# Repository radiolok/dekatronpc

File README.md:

# DekatronPC

Ламповый компьютер на декатронах А110 с системой команд Brainfuck. Счётчики машины — реверсивные декатроны: они умеют ровно то, что нужно Brainfuck, — прибавить и отнять единицу. Логика вокруг них — вакуумные лампы 6Н16Б и 6Ж2Б, без кремниевых полупроводников в вычислительном тракте.

*A vacuum-tube Brainfuck computer built around A110 dekatron counting tubes. RTL in SystemVerilog, an FPGA emulator for blocks not yet built, requirements and microarchitecture docs in Russian.*

## Машина

| Параметр | Значение |
|---|---|
| Архитектура | гарвардская: отдельные память программ и память данных |
| Система команд | один набор из 16 опкодов (ISA16): Brainfuck и шесть служебных, 4 бита на команду |
| Счётчик команд IP | 5 декатронов, 0…99999 |
| Счётчик вложенности Loop | 2 декатрона, 0…99; переполнение — аппаратная ошибка, машина замирает до сброса |
| Указатель данных AP | 5 декатронов; в RTL счёт замыкается 0 ↔ 99999 (предел 29999 — открытый вопрос OPEN-001) |
| Значение ячейки Data | 3 декатрона, 0…255 |
| Всего декатронов | 15 |
| Память программ | 100 000 × 4 бит, верхняя декада 99990…99999 — ПЗУ загрузчика |
| Память данных | 100 000 ячеек × 10 бит (BCD: сотни, десятки, единицы); физически — ферритовые кубы КП128/17-М70, до их установки память играет эмулятор на ПЛИС |
| Тактовая частота | 100 кГц (сборка по умолчанию; статический анализ по SPICE-задержкам ламп даёт минимальный период ≈ 9 мкс; тайминги самого декатрона — OPEN-013/014) |
| Логика | ≈ 1070 ламп + 15 декатронов А110 по синтезу RTL в библиотеку спроектированных ламповых ячеек (среднее по четырём зёрнам ABC, ±10), без памяти; бюджет 1200, цель — меньше 1000 |

Адреса и данные хранятся в BCD прямо так, как их показывают декатроны: память адресуется тетрадами без перевода в двоичный код. Цикл просматривается самой линией выборки: при `[` с нулевой ячейкой или `]` с ненулевой IP проматывается до парной скобки, счётчик Loop считает вложенность.

Конфигурация счётчиков проверена на наборе из ста реальных программ с GitHub — [Brainfuck-100](https://github.com/radiolok/bfutils/tree/master/programs/bf100) в сабмодуле `bfutils`: в 5 + 2 + 5 + 3 декатрона помещаются 97 программ из 100.

## Система команд

Один 4-битный набор, режимов нет (ISA16, [doc/isa16.md](doc/isa16.md)). Коды 0x0…0xA — Brainfuck.

| Опкод | Символ | Команда |
|---|---|---|
| 0x0 | `N` | NOP |
| 0x1 | `H` | HALT |
| 0x2 / 0x3 | `+` `-` | INC / DEC ячейки |
| 0x4 / 0x5 | `>` `<` | AINC / ADEC |
| 0x6 / 0x7 | `[` `]` | цикл по нулю ячейки |
| 0x8 / 0x9 | `.` `,` | COUT / CIN |
| 0xA | `0` | `[-]` — ячейка ← 0 (ставит MemLock) |
| 0xB | `S` / `E` | LD — начало загрузки; в потоке загрузки — её конец (EOT), в память не пишется |
| 0xC | `A` | CLRA — AP ← 0 |
| 0xD | `P` | MemLock — ставит флаг MemLock без загрузки: ячейка ← счётчик данных (копирование `>P<`) |
| 0xE / 0xF | `{` `}` | цикл по нулю AP (нужен загрузчику) |

Промотка считает `[ ]` и `{ }` вместе, поэтому вкладывать один вид в другой нельзя. Аппаратный сброс ставит IP = 99990 и запускает загрузчик `0<{0<}` … LD из верхней декады памяти программ, защищённой от записи (очистка памяти данных и загрузка с адреса 0); программный сброс обнуляет все счётчики, в том числе IP. EOT запускает программный сброс. Полная семантика, MemLock и ленивое чтение памяти данных — в [TRS.md](TRS.md), разделы 6–10.

## Документы

| Документ | Что в нём |
|---|---|
| [TRS.md](TRS.md) | требования: архитектура, ISA, память, декатроны, RTL, верификация, стенд, ламповые модули, открытые вопросы, чек-лист и план работ. Каждое требование имеет ID (`REQ-*`, `OPEN-*`) и статус |
| [SCHEMES.md](SCHEMES.md) | структурные схемы ядра в семи листах: декатрон, модуль, счётчик, IpLine, ApLine, MachineCtrl, верхний уровень |
| [doc/dpcrun_golden_model.md](doc/dpcrun_golden_model.md) | C++ golden model: семантика, расхождения RTL и TRS, найденные дефекты |
| [tb/README.md](tb/README.md) | testbench на cocotb и pyuvm |
| [doc/isa16.md](doc/isa16.md) | система команд ISA16 и выбор между вариантами |
| [doc/tube_count_below_1000.md](doc/tube_count_below_1000.md) | путь подсчёта ламп: что сделано и что отвергнуто (ранее — `doc/tube_count_reduction.md`, `doc/tube_count_1000.md`) |
| [sch/logic/README.md](sch/logic/README.md) | библиотека ламповых ячеек: SPICE, схемы KiCad, страницы ячеек; метод — [doc/cell_design_method.md](doc/cell_design_method.md) |
| [doc/vtube_sta.md](doc/vtube_sta.md), [doc/synth_sim.md](doc/synth_sim.md) | статический анализ времён и симуляция нетлиста с задержками ламп |
| [rtl/DekatronPC/Dekatron/DekatronCounter.md](rtl/DekatronPC/Dekatron/DekatronCounter.md) | устройство декатронного счётчика |
| [rtl/DekatronPC/emulator_inspection.md](rtl/DekatronPC/emulator_inspection.md) | разбор слоя эмулятора на ПЛИС |
| [history.md](history.md) | журнал сессий работы над проектом |

## Репозиторий

| Путь | Содержимое |
|---|---|
| `rtl/DekatronPC/` | ядро: `DekatronPC.sv`, `MachineCtrl.sv`, `IpLine.sv`, `ApLine.sv`, `IpMemory.sv`, `RAM.sv`, верх для DE0-Nano `De0Nano.sv` |
| `rtl/DekatronPC/Dekatron/` | декатрон: модель лампы `DekatronTubeV2`, модуль, счётчик, генератор фаз, формирователь импульсов |
| `rtl/parameters.sv` | разрядность счётчиков |
| `rtl/Emulator/` | слой эмулятора на ПЛИС: клавиатура, индикатор МС6205, ИН-12, загрузчик прошивки |
| `rtl/Logic/`, `rtl/Functions/` | примитивы и кодеры |
| `sch/logic/` | ламповые логические ячейки, по папке на ячейку (схема, тестбенч, описание, картинки; перечень в `sch/logic/README.md`), и библиотека ячеек для синтеза `vtube_cells.lib` / `vtube_cells.v` / `vtube_timing.json` |
| `rtl/programs/` | тестовые программы `*.bfk` и загрузчик |
| `rtl/run/` | скрипты моделирования, синтеза и подсчёта ламп |
| `rtl/quartus/` | проект Quartus |
| `tb/` | testbench на cocotb и pyuvm |
| `bfutils/` | сабмодуль [radiolok/bfutils](https://github.com/radiolok/bfutils): компилятор, эмулятор, golden model `dpcrun`, набор Brainfuck-100 |
| `sch/` | схемы KiCad: эмулятор, экспериментальная декатронная ячейка, библиотеки ламп, ферритовая память (`sch/fcore`), блок питания стенда (`sch/stand`) |
| `doc/` | отчёты и справочная литература |
| `img/schemes/` | картинки для SCHEMES.md |
| `web/` | симулятор в браузере: пульт, декатроны, загрузка по SOT/EOT, Brainfuck-100 ([web/README.md](web/README.md)) |
| `tools/` | `spice/` (расчёт ячеек), `kicad/` (генераторы схем), `digitize/` (оцифровка справочников), `netview/` (схемы нетлиста), `synth/`, `bf100/` |
| `tools/schemes/` | генератор SCHEMES.md и картинок схем: `python3 tools/schemes/build.py` |

Блоки `Dekatron.sv`, `DekatronPulseAllow`, `DekatronCarrySignal`, `InsnDecoder`, `BcdToBinEnc` в тракте памяти и папка `rtl/[DEPRECATED]` — старый тракт, подлежит удалению (TRS, раздел 19.4).

## Сборка и проверка

```bash
git clone --recursive https://github.com/radiolok/dekatronpc.git
cd dekatronpc
git submodule update --init       # если клонировали без --recursive

docker build -t dekatron-pc .     # Verilator, Icarus, Yosys, cocotb — то же окружение, что в CI
# Quartus собирается отдельно: ./rtl/run/build_fpga.sh, CI — .github/workflows/fpga.yml
```

| Задача | Команда |
|---|---|
| один тест на Icarus | `cd tb && make test_compare SIM=icarus` |
| регрессия cocotb | `cd tb && make regression` |
| моделирование RTL | `cd rtl/run && ./run_tests.sh -t` |
| то же с моделью задержек ламп | `cd rtl/run && ./run_tests.sh -d` |
| синтез в лампы (Yosys), подсчёт ламп | `cd rtl/run && ./run_tests.sh -s` |
| RTL-тесты на нетлисте (`-t` — с задержками ламп) | `cd rtl/run && ./synth_sim.sh [-t]` |

Полная сборка DekatronPC и эмулятора в Verilator и синтез — тяжёлые задачи; на слабой машине начинайте с одиночных целей на Icarus. CI: `.github/workflows/` (`docker-image.yml`, `fpga.yml`, `web.yml`, `pages.yml`).

## Состояние

Версия требований — TRS v0.53 (2026-11-04).

- Готово в RTL: ISA16, модель декатрона и счётчик с завершением операции в такте приёма, IpLine / ApLine / MachineCtrl с предвыборкой и MemLock, банковая память, загрузчик в верхней декаде, терминал по UART.
- Проверка: golden model `bfutils/dpcrun` совпадает с RTL шаг в шаг (pi.bfk — 221 386 шагов, вывод `3.141`); cocotb, Icarus, Verilator, синтез и симуляция нетлиста (в том числе с задержками ламп из SPICE) идут в CI; есть симулятор в браузере.
- Ламповые ячейки (NOR, NAND, AOI, защёлки, триггеры) рассчитаны в SPICE и нарисованы в KiCad; на железе подтверждены только отдельные измерения (ёмкость ламп, блок питания).
- Открыто: OPEN-001 (предел AP), OPEN-007 (BELL), OPEN-011, OPEN-012, OPEN-013/014 (тайминги декатрона), OPEN-018. Следующие этапы: P&R-инструмент (REQ-PR-*), платы модуля декатрона, испытательный стенд, ферритовая память, первые ламповые модули.

Полный чек-лист — в TRS.md, разделы 19–22.

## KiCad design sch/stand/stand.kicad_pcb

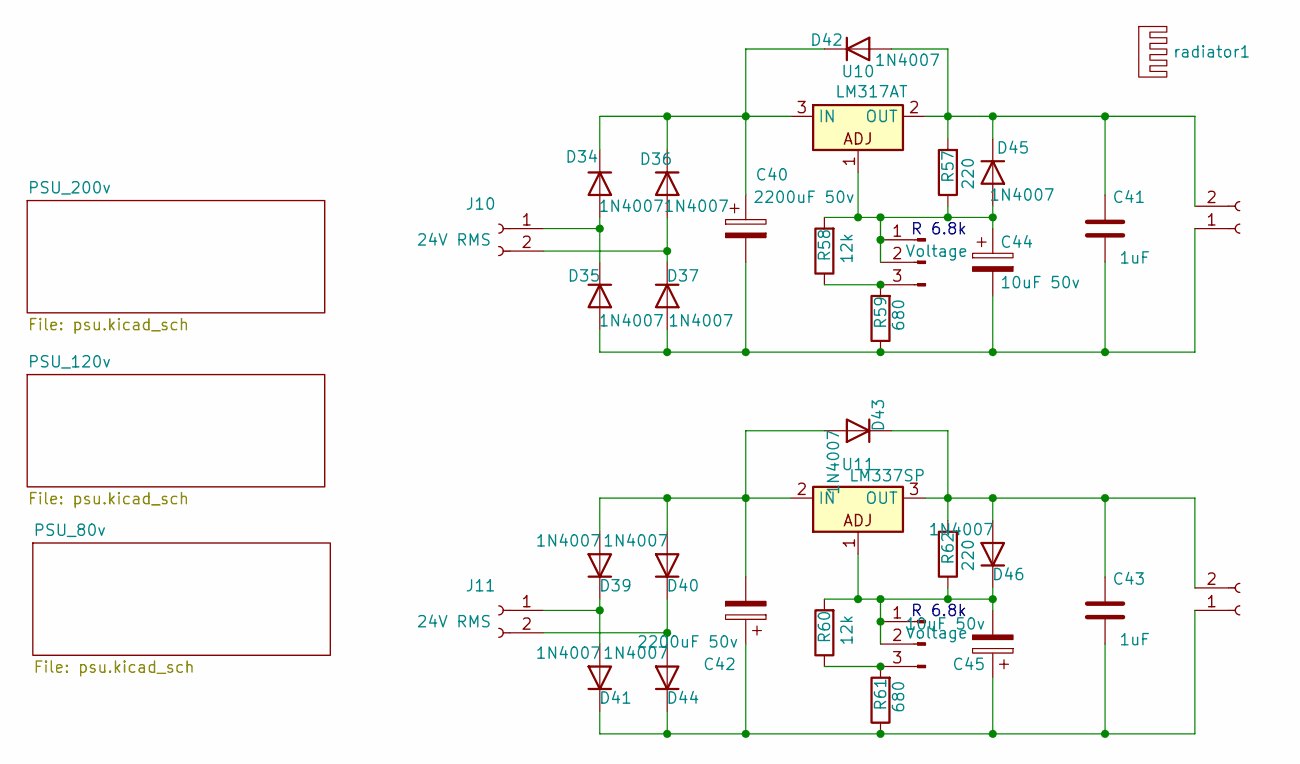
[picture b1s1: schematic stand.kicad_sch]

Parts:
C40, C42: 2200uF 50v; CP_Radial_D18.0mm_P7.50mm
C41, C43: 1uF; C_Axial_L3.8mm_D2.6mm_P7.50mm_Horizontal
C44, C45: 10uF 50v; CP_Radial_D10.0mm_P3.50mm
D34, D35, D36, D37, D39, D40, D41, D42, D43, D44, D45, D46: 1N4007; D_DO-41_SOD81_P10.16mm_Horizontal
J10, J11: 24V RMS; TerminalBlock_Phoenix_MKDS-1,5-2-5.08_1x02_P5.08mm_Horizont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
J12, J13: Vout; TerminalBlock_Phoenix_MKDS-1,5-2-5.08_1x02_P5.08mm_Horizont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
J14, J15: Voltage; PinHeader_1x03_P2.54mm_Vertical
R57, R62: 220; R_Axial_DIN0207_L6.3mm_D2.5mm_P7.62mm_Horizontal
R58, R60: 12k; R_Axial_DIN0207_L6.3mm_D2.5mm_P7.62mm_Horizontal
R59, R61: 680; R_Axial_DIN0207_L6.3mm_D2.5mm_P7.62mm_Horizontal
U10: LM317AT; TO-220-3_Vertical
U11: LM337SP; TO-220-3_Vertical
radiator1: Радиатор

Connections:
unnamed: D34.2 (A), D35.1 (K), J10.1
unnamed: C40.1, D34.1 (K), D36.1 (K), D42.1 (K), U10.3 (IN)
unnamed: C40.2, C41.2, C44.2, D35.2 (A), D37.2 (A), J12.1, R59.1
unnamed: D36.2 (A), D37.1 (K), J10.2
unnamed: C42.2, D39.2 (A), D40.2 (A), D43.2 (A), U11.2 (IN)
unnamed: D39.1 (K), D41.2 (A), J11.1
unnamed: D40.1 (K), D44.2 (A), J11.2
unnamed: C42.1, C43.2, C45.1, D41.1 (K), D44.1 (K), J13.1, R61.1
unnamed: C41.1, D42.2 (A), D45.1 (K), J12.2, R57.2, U10.2 (OUT)
unnamed: C43.1, D43.1 (K), D46.2 (A), J13.2, R62.2, U11.3 (OUT)
unnamed: C44.1, D45.2 (A), J14.1, J14.2, R57.1, R58.2, U10.1
unnamed: C45.2, D46.1 (K), J15.1, J15.2, R60.2, R62.1, U11.1
unnamed: J14.3, R58.1, R59.2
unnamed: J15.3, R60.1, R61.2

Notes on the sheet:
R 6.8k

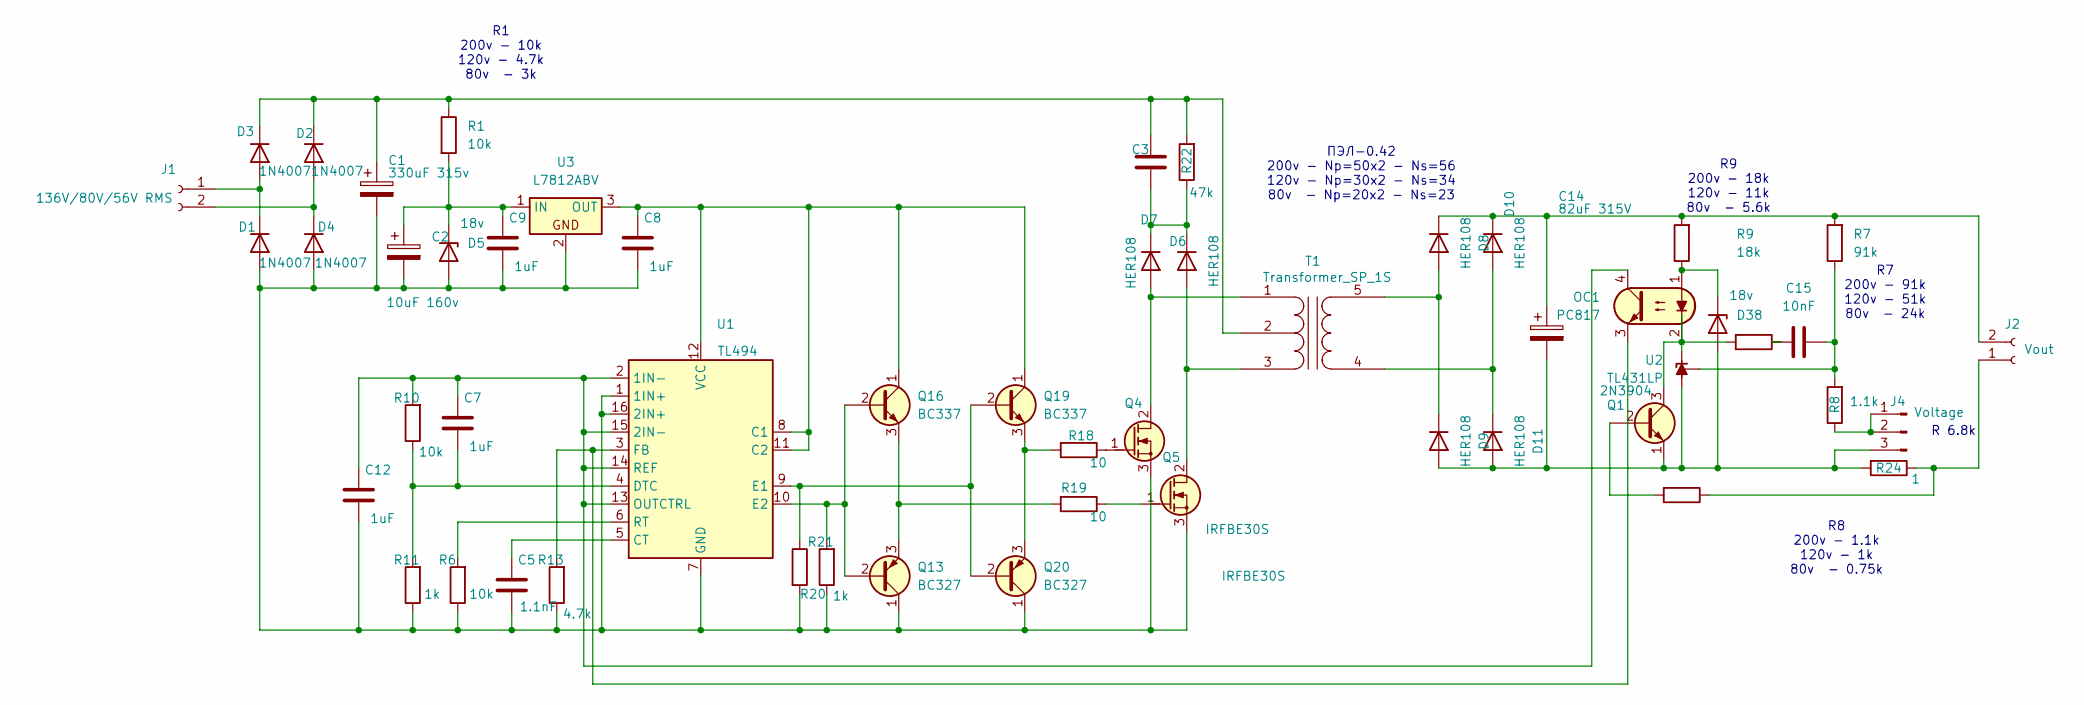
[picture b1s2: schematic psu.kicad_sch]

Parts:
C1: 330uF 315v; CP_Radial_D30.0mm_P10.00mm_SnapIn
C2: 10uF 160v; CP_Radial_D10.0mm_P3.50mm
C3: 10nF 630v; C_Rect_L11.5mm_W6.4mm_P10.00mm_MKT
C5: 1.1nF; C_Axial_L3.8mm_D2.6mm_P7.50mm_Horizontal
C7, C8, C9, C12: 1uF; C_Axial_L3.8mm_D2.6mm_P7.50mm_Horizontal
C14: 82uF 315V; CP_Radial_D18.0mm_P7.50mm
C15: 10nF; C_Rect_L7.0mm_W2.5mm_P5.00mm
D1, D2, D3, D4: 1N4007; D_DO-41_SOD81_P10.16mm_Horizontal
D5, D38: 18v; D_DO-35_SOD27_P7.62mm_Horizontal
D6, D7, D8, D9, D10, D11: HER108; D_DO-41_SOD81_P10.16mm_Horizontal
J1: 136V/80V/56V RMS; TerminalBlock_Phoenix_MKDS-1,5-2-5.08_1x02_P5.08mm_Horizont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
J2: Vout; TerminalBlock_Phoenix_MKDS-1,5-2-5.08_1x02_P5.08mm_Horizont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
J4: Voltage; PinHeader_1x03_P2.54mm_Vertical
OC1: PC817; DIP-4_W7.62mm_LongPads
Q1: 2N3904; TO-92_Inline_Wide_EBC
Q4, Q5: IRFBE30S; TO-263-2
Q13, Q20: BC327; TO-92_Inline_Wide_CBE
Q16, Q19: BC337; TO-92_Inline_Wide_CBE
R1: 10k; R_Axial_DIN0918_L18.0mm_D9.0mm_P25.40mm_Horizontal
R6, R10: 10k; R_Axial_DIN0207_L6.3mm_D2.5mm_P7.62mm_Horizontal
R7: 91k; R_Axial_DIN0516_L15.5mm_D5.0mm_P5.08mm_Vertical
R8: 1.1k; R_Axial_DIN0207_L6.3mm_D2.5mm_P7.62mm_Horizontal
R9: 18k; R_Axial_DIN0516_L15.5mm_D5.0mm_P5.08mm_Vertical
R11: 1k; R_Axial_DIN0207_L6.3mm_D2.5mm_P7.62mm_Horizontal
R13: 4.7k; R_Axial_DIN0207_L6.3mm_D2.5mm_P7.62mm_Horizontal
R18, R19: 10; R_Axial_DIN0207_L6.3mm_D2.5mm_P7.62mm_Horizontal
R20, R21: 1k; R_Axial_DIN0617_L17.0mm_D6.0mm_P7.62mm_Vertical
R22: 47k; R_Axial_DIN0414_L11.9mm_D4.5mm_P15.24mm_Horizontal
R24: 1; R_Axial_DIN0411_L9.9mm_D3.6mm_P15.24mm_Horizontal
R25: 100; R_Axial_DIN0207_L6.3mm_D2.5mm_P7.62mm_Horizontal
R51: 470; R_Axial_DIN0207_L6.3mm_D2.5mm_P7.62mm_Horizontal
T1: Transformer_SP_1S; EL33
U1: TL494; DIP-16_W7.62mm
U2: TL431LP; TO-92_Inline_Wide
U3: L7812ABV; TO-220-3_Vertical

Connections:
unnamed: C15.1, R25.1
unnamed: C1.2, C2.2, C5.2, C8.2, C9.2, C12.2, D1.2 (A), D4.2 (A), D5.2 (A), Q4.3 (S), Q5.3 (S), Q13.1 (C), Q20.1 (C), R6.1, R11.1, R13.1, R20.2, R21.1, U1.1 (1IN+), U1.7 (GND), U1.16 (2IN+), U3.2
unnamed: D1.1 (K), D3.2 (A), J1.1
unnamed: D2.2 (A), D4.1 (K), J1.2
unnamed: C1.1, C3.1, D2.1 (K), D3.1 (K), R1.1, R22.2, T1.2 (PM)
unnamed: C2.1, C9.1, D5.1 (K), R1.2, U3.1 (IN)
unnamed: D6.2 (A), Q5.2 (D), T1.3 (PR2)
unnamed: C3.2, D6.1 (K), D7.1 (K), R22.1
unnamed: D7.2 (A), Q4.2 (D), T1.1 (PR1)
unnamed: D8.2 (A), D9.1 (K), T1.5 (S2)
unnamed: D10.2 (A), D11.1 (K), T1.4 (S1)
unnamed: C14.1, D8.1 (K), D10.1 (K), J2.2, R7.2, R9.2
unnamed: C14.2, D9.2 (A), D11.2 (A), D38.2 (A), J4.3, Q1.1 (E), R24.2, U2.2 (A)
unnamed: D38.1 (K), OC1.1, R9.1
unnamed: J2.1, R24.1, R51.1
unnamed: J4.1, J4.2, R8.1
unnamed: Q1.2 (B), R51.2
unnamed: OC1.2, Q1.3 (C), R25.2, U2.3 (K)
unnamed: Q4.1 (G), R18.1
unnamed: Q5.1 (G), R19.1
unnamed: Q13.2 (B), Q16.2 (B), R21.2, U1.10 (E2)
unnamed: Q13.3 (E), Q16.3 (E), R19.2
unnamed: C8.1, Q16.1 (C), Q19.1 (C), U1.8 (C1), U1.11 (C2), U1.12 (VCC), U3.3 (OUT)
unnamed: Q19.2 (B), Q20.2 (B), R20.1, U1.9 (E1)
unnamed: Q19.3 (E), Q20.3 (E), R18.2
unnamed: C7.1, C12.1, OC1.4, R10.2, U1.2 (1IN-), U1.13 (OUTCTRL), U1.14 (REF), U1.15 (2IN-)
unnamed: C5.1, U1.5 (CT)
unnamed: C7.2, R10.1, R11.2, U1.4 (DTC)
unnamed: OC1.3, R13.2, U1.3 (FB)
unnamed: R6.2, U1.6 (RT)
unnamed: C15.2, R7.1, R8.2, U2.1 (REF)

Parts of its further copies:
C4, C28: 330uF 315v; CP_Radial_D30.0mm_P10.00mm_SnapIn
C6, C29: 10uF 160v; CP_Radial_D10.0mm_P3.50mm
C16, C17, C18, C20, C27, C30, C31, C33: 1uF; C_Axial_L3.8mm_D2.6mm_P7.50mm_Horizontal
C19, C32: 1.1nF; C_Axial_L3.8mm_D2.6mm_P7.50mm_Horizontal
C23, C36: 10nF 630v; C_Rect_L11.5mm_W6.4mm_P10.00mm_MKT
C25, C38: 82uF 315V; CP_Radial_D18.0mm_P7.50mm
C26, C39: 10nF; C_Rect_L7.0mm_W2.5mm_P5.00mm
D12, D13, D14, D15, D23, D24, D25, D26: 1N4007; D_DO-41_SOD81_P10.16mm_Horizontal
D16, D27, D47, D48: 18v; D_DO-35_SOD27_P7.62mm_Horizontal
D17, D18, D19, D20, D21, D22, D28, D29, D30, D31, D32, D33: HER108; D_DO-41_SOD81_P10.16mm_Horizontal
J3, J7: 136V/80V/56V RMS; TerminalBlock_Phoenix_MKDS-1,5-2-5.08_1x02_P5.08mm_Horizont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
J5, J8: Voltage; PinHeader_1x03_P2.54mm_Vertical
J6, J9: Vout; TerminalBlock_Phoenix_MKDS-1,5-2-5.08_1x02_P5.08mm_Horizont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
OC2, OC3: PC817; DIP-4_W7.62mm_LongPads
Q2, Q3: 2N3904; TO-92_Inline_Wide_EBC
Q6, Q7, Q8, Q9: IRFBE30S; TO-263-2
Q14, Q15, Q22, Q24: BC327; TO-92_Inline_Wide_CBE
Q17, Q18, Q21, Q23: BC337; TO-92_Inline_Wide_CBE
R2, R3: 10k; R_Axial_DIN0918_L18.0mm_D9.0mm_P25.40mm_Horizontal
R12, R15, R36, R38: 10k; R_Axial_DIN0207_L6.3mm_D2.5mm_P7.62mm_Horizontal
R14, R37: 1k; R_Axial_DIN0207_L6.3mm_D2.5mm_P7.62mm_Horizontal
R16, R39: 4.7k; R_Axial_DIN0207_L6.3mm_D2.5mm_P7.62mm_Horizontal
R17, R46: 18k; R_Axial_DIN0516_L15.5mm_D5.0mm_P5.08mm_Vertical
R26, R27, R40, R41: 1k; R_Axial_DIN0617_L17.0mm_D6.0mm_P7.62mm_Vertical
R28, R29, R42, R43: 10; R_Axial_DIN0207_L6.3mm_D2.5mm_P7.62mm_Horizontal
R30, R44: 47k; R_Axial_DIN0414_L11.9mm_D4.5mm_P15.24mm_Horizontal
R32, R47: 100; R_Axial_DIN0207_L6.3mm_D2.5mm_P7.62mm_Horizontal
R33, R48: 91k; R_Axial_DIN0516_L15.5mm_D5.0mm_P5.08mm_Vertical
R34, R49: 1.1k; R_Axial_DIN0207_L6.3mm_D2.5mm_P7.62mm_Horizontal
R35, R50: 1; R_Axial_DIN0411_L9.9mm_D3.6mm_P15.24mm_Horizontal
R52, R53: 470; R_Axial_DIN0207_L6.3mm_D2.5mm_P7.62mm_Horizontal
T2, T3: Transformer_SP_1S; EL33
U4, U7: L7812ABV; TO-220-3_Vertical
U5, U8: TL494; DIP-16_W7.62mm
U6, U9: TL431LP; TO-92_Inline_Wide

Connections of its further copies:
unnamed: C26.1, R32.1
unnamed: C39.1, R47.1
unnamed: D12.2 (A), D13.1 (K), J3.1
unnamed: C4.1, C23.1, D12.1 (K), D14.1 (K), R2.1, R30.2, T2.2 (PM)
unnamed: C4.2, C6.2, C16.2, C18.2, C19.2, C20.2, D13.2 (A), D15.2 (A), D16.2 (A), Q6.3 (S), Q7.3 (S), Q14.1 (C), Q22.1 (C), R14.1, R15.1, R16.1, R26.2, R27.1, U4.2, U5.1 (1IN+), U5.7 (GND), U5.16 (2IN+)
unnamed: D14.2 (A), D15.1 (K), J3.2
unnamed: C6.1, C18.1, D16.1 (K), R2.2, U4.1 (IN)
unnamed: D17.2 (A), Q6.2 (D), T2.1 (PR1)
unnamed: C23.2, D17.1 (K), D18.1 (K), R30.1
unnamed: D18.2 (A), Q7.2 (D), T2.3 (PR2)
unnamed: D19.2 (A), D20.1 (K), T2.5 (S2)
unnamed: C25.1, D19.1 (K), D21.1 (K), J6.2, R17.2, R33.2
unnamed: C25.2, D20.2 (A), D22.2 (A), D47.2 (A), J5.3, Q2.1 (E), R35.2, U6.2 (A)
unnamed: D21.2 (A), D22.1 (K), T2.4 (S1)
unnamed: D23.2 (A), D24.1 (K), J7.1
unnamed: C28.1, C36.1, D23.1 (K), D25.1 (K), R3.1, R44.2, T3.2 (PM)
unnamed: C27.2, C28.2, C29.2, C31.2, C32.2, C33.2, D24.2 (A), D26.2 (A), D27.2 (A), Q8.3 (S), Q9.3 (S), Q15.1 (C), Q24.1 (C), R37.1, R38.1, R39.1, R40.2, R41.1, U7.2, U8.1 (1IN+), U8.7 (GND), U8.16 (2IN+)
unnamed: D25.2 (A), D26.1 (K), J7.2
unnamed: C29.1, C31.1, D27.1 (K), R3.2, U7.1 (IN)
unnamed: D28.2 (A), Q8.2 (D), T3.1 (PR1)
unnamed: C36.2, D28.1 (K), D29.1 (K), R44.1
unnamed: D29.2 (A), Q9.2 (D), T3.3 (PR2)
unnamed: D30.2 (A), D31.1 (K), T3.5 (S2)
unnamed: C38.1, D30.1 (K), D32.1 (K), J9.2, R46.2, R48.2
unnamed: C38.2, D31.2 (A), D33.2 (A), D48.2 (A), J8.3, Q3.1 (E), R50.2, U9.2 (A)
unnamed: D32.2 (A), D33.1 (K), T3.4 (S1)
unnamed: D47.1 (K), OC2.1, R17.1
unnamed: D48.1 (K), OC3.1, R46.1
unnamed: J5.1, J5.2, R34.1
unnamed: J6.1, R35.1, R52.1
unnamed: J8.1, J8.2, R49.1
unnamed: J9.1, R50.1, R53.1
unnamed: Q2.2 (B), R52.2
unnamed: OC2.2, Q2.3 (C), R32.2, U6.3 (K)
unnamed: Q3.2 (B), R53.2
unnamed: OC3.2, Q3.3 (C), R47.2, U9.3 (K)
unnamed: Q6.1 (G), R28.1
unnamed: Q7.1 (G), R29.1
unnamed: Q8.1 (G), R42.1
unnamed: Q9.1 (G), R43.1
unnamed: Q14.2 (B), Q17.2 (B), R27.2, U5.10 (E2)
unnamed: Q14.3 (E), Q17.3 (E), R29.2
unnamed: Q15.2 (B), Q18.2 (B), R41.2, U8.10 (E2)
unnamed: Q15.3 (E), Q18.3 (E), R43.2
unnamed: C20.1, Q17.1 (C), Q21.1 (C), U4.3 (OUT), U5.8 (C1), U5.11 (C2), U5.12 (VCC)
unnamed: C33.1, Q18.1 (C), Q23.1 (C), U7.3 (OUT), U8.8 (C1), U8.11 (C2), U8.12 (VCC)
unnamed: Q21.2 (B), Q22.2 (B), R26.1, U5.9 (E1)
unnamed: Q21.3 (E), Q22.3 (E), R28.2
unnamed: Q23.2 (B), Q24.2 (B), R40.1, U8.9 (E1)
unnamed: Q23.3 (E), Q24.3 (E), R42.2
unnamed: C16.1, C17.1, OC2.4, R12.2, U5.2 (1IN-), U5.13 (OUTCTRL), U5.14 (REF), U5.15 (2IN-)
unnamed: C19.1, U5.5 (CT)
unnamed: C17.2, R12.1, R14.2, U5.4 (DTC)
unnamed: OC2.3, R16.2, U5.3 (FB)
unnamed: R15.2, U5.6 (RT)
unnamed: C26.2, R33.1, R34.2, U6.1 (REF)
unnamed: C27.1, C30.1, OC3.4, R36.2, U8.2 (1IN-), U8.13 (OUTCTRL), U8.14 (REF), U8.15 (2IN-)
unnamed: C32.1, U8.5 (CT)
unnamed: C30.2, R36.1, R37.2, U8.4 (DTC)
unnamed: OC3.3, R39.2, U8.3 (FB)
unnamed: R38.2, U8.6 (RT)
unnamed: C39.2, R48.1, R49.2, U9.1 (REF)

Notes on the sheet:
ПЭЛ-0.42 200v - Np=50x2 - Ns=56 120v - Np=30x2 - Ns=34 80v - Np=20x2 - Ns=23
R 6.8k
R8 200v - 1.1k 120v - 1k 80v - 0.75k
R1 200v - 10k 120v - 4.7k 80v - 3k
R7 200v - 91k 120v - 51k 80v - 24k
R9 200v - 18k 120v - 11k 80v - 5.6k

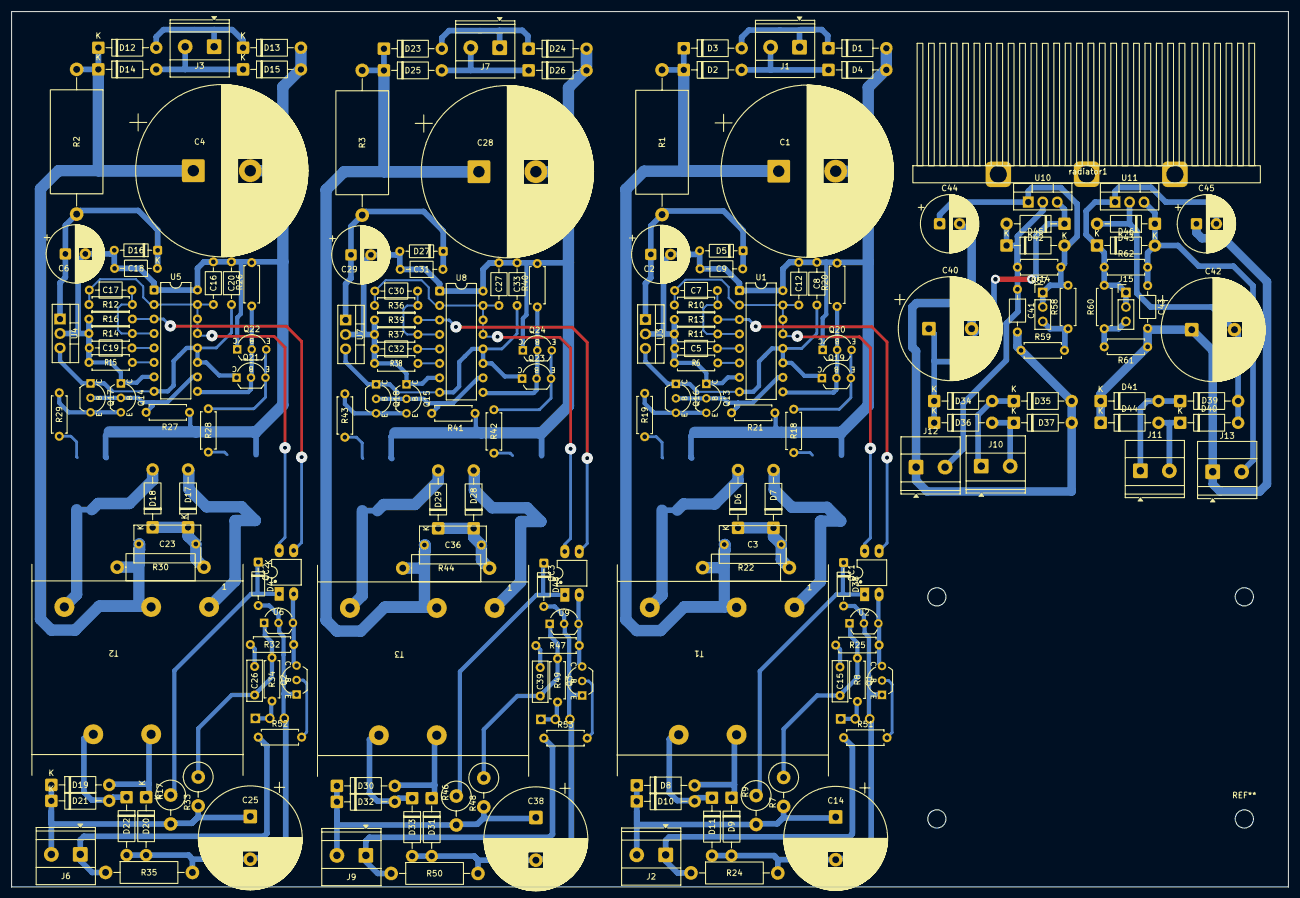
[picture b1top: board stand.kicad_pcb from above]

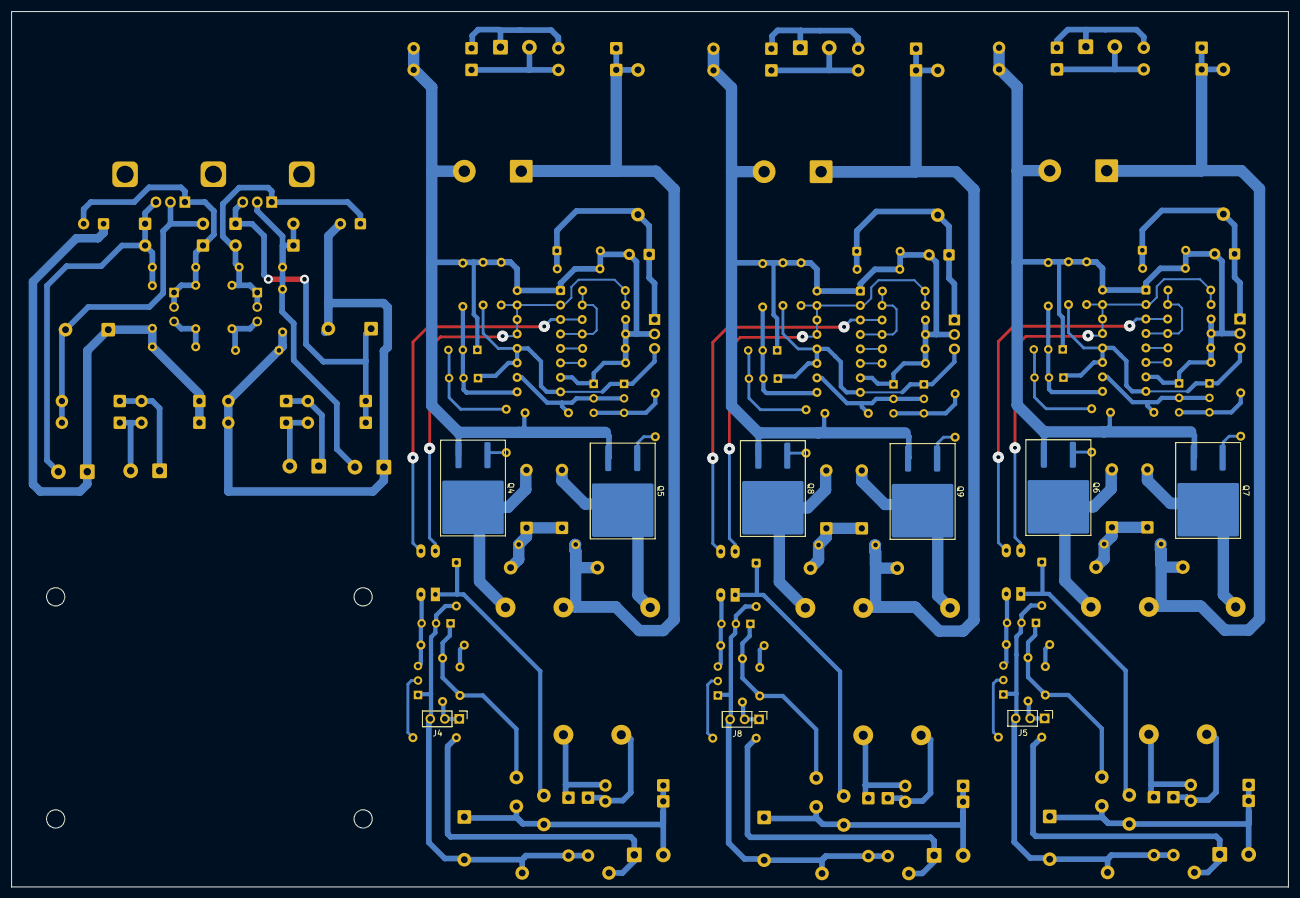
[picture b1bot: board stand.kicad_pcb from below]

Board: 2 copper layers, 224.2 x 153.7 mm, 192 parts (9 on the bottom side), 107 nets.

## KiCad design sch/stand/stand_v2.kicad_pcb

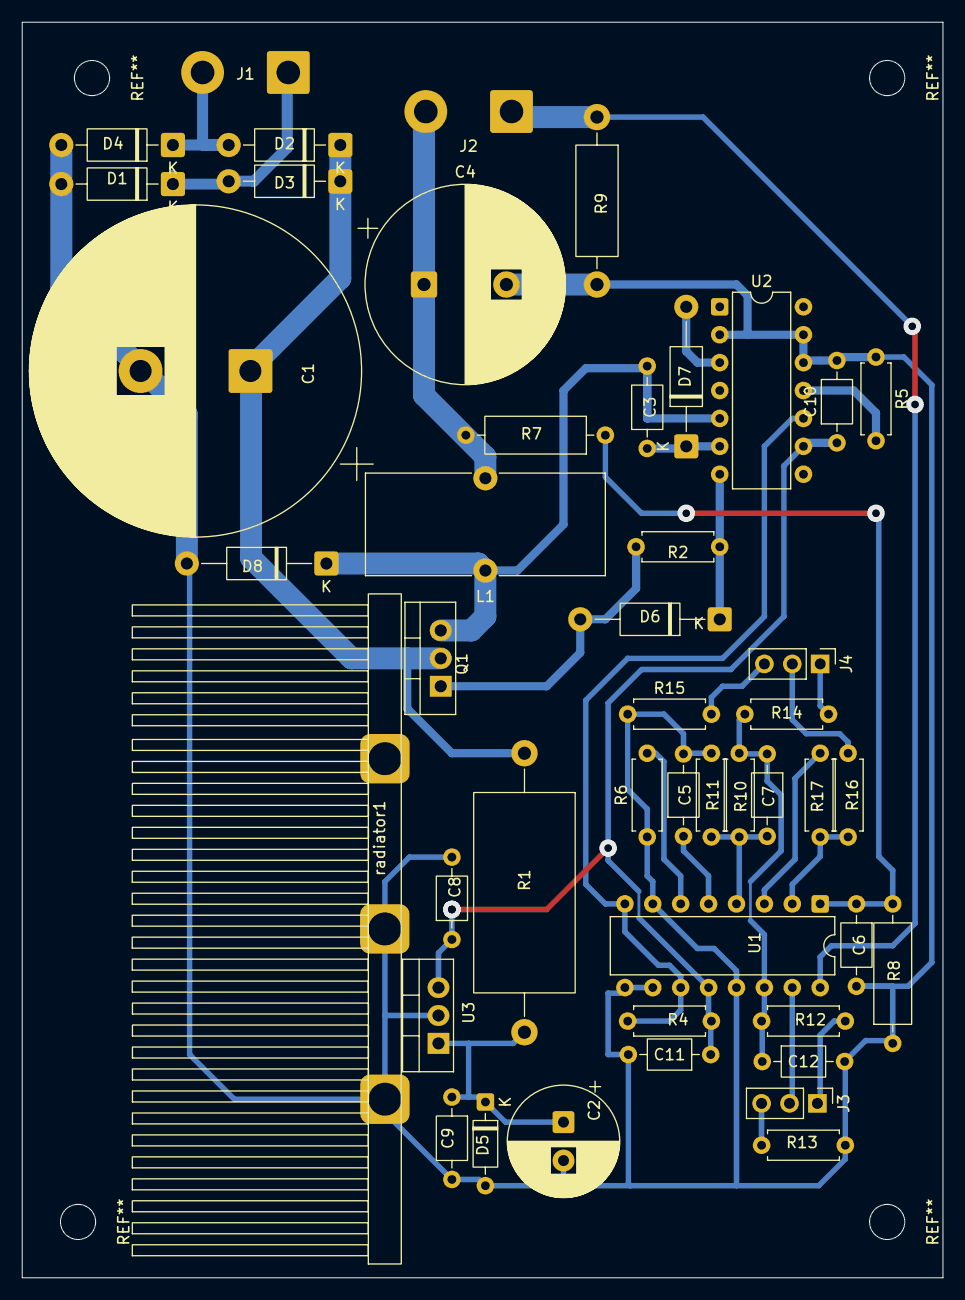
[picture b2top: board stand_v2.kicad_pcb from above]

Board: 2 copper layers, 83.8 x 114.3 mm, 46 parts (0 on the bottom side), 28 nets.

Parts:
C1: C_Polarized; CP_Radial_D30.0mm_P10.00mm_SnapIn
C2: C_Polarized; CP_Radial_D10.0mm_P3.50mm
C3, C6, C7, C8, C9, C10, C11, C12: 1uF; C_Axial_L3.8mm_D2.6mm_P7.50mm_Horizontal
C4: C_Polarized; CP_Radial_D18.0mm_P7.50mm
C5: 2.2nF; C_Axial_L3.8mm_D2.6mm_P7.50mm_Horizontal
D1, D2, D3, D4: 1N4007; D_DO-41_SOD81_P10.16mm_Horizontal
D5: D_Zener; D_DO-35_SOD27_P7.62mm_Horizontal
D6, D7, D8: UF4007; D_DO-41_SOD81_P12.70mm_Horizontal
J1, J2: Conn_01x02_Socket; SolderWire-1.5sqmm_1x02_P7.8mm_D1.7mm_OD3.9mm
J3: Current; PinHeader_1x03_P2.54mm_Vertical
J4: Voltage; PinHeader_1x03_P2.54mm_Vertical
L1: L; L_Toroid_Vertical_L21.6mm_W9.1mm_P8.40mm_Bourns_5700
Q1: IRF840A; TO-220-3_Vertical
R1: R; R_Axial_DIN0918_L18.0mm_D9.0mm_P25.40mm_Horizontal
R2: 20; R_Axial_DIN0207_L6.3mm_D2.5mm_P7.62mm_Horizontal
R4, R11: 1k; R_Axial_DIN0207_L6.3mm_D2.5mm_P7.62mm_Horizontal
R5, R6, R10: 10k; R_Axial_DIN0207_L6.3mm_D2.5mm_P7.62mm_Horizontal
R7, R8: ?; R_Axial_DIN0309_L9.0mm_D3.2mm_P12.70mm_Horizontal
R9: 1; R_Axial_DIN0411_L9.9mm_D3.6mm_P15.24mm_Horizontal
R12, R13, R14, R15: ?; R_Axial_DIN0207_L6.3mm_D2.5mm_P7.62mm_Horizontal
R16: 510; R_Axial_DIN0207_L6.3mm_D2.5mm_P7.62mm_Horizontal
R17: 51k; R_Axial_DIN0207_L6.3mm_D2.5mm_P7.62mm_Horizontal
U1: TL494; DIP-16_W7.62mm
U2: IR2110; DIP-14_W7.62mm
U3: L7812ABV; TO-220-3_Vertical
radiator1: Радиатор

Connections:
+5V: C7.1, C12.1, R10.2, R12.2, R14.2, U1.14 (REF)
+12V: C8.1, C10.1, C11.1, R4.2, U1.12 (VCC), U2.9 (VDD), U3.3 (OUT)
+18V: C2.1, C9.1, D5.1 (K), R1.2, U3.1 (IN)
GND: C1.2, C2.2, C4.2, C5.2, C6.2, C8.2, C9.2, C10.2, C11.2, C12.2, D1.2 (A), D4.2 (A), D5.2 (A), D8.2 (A), R5.1, R6.1, R8.1, R9.2, R11.1, R13.1, R15.1, U1.7 (GND), U1.9 (E1), U1.10 (E2), U1.13 (OUTCTRL), U2.2 (COM), U2.12 (LIN), U2.13 (VSS), U3.2
unnamed: D1.1 (K), D3.2 (A), J1.1
unnamed: D2.2 (A), D4.1 (K), J1.2
unnamed: D6.2 (A), Q1.1 (G), R2.2
unnamed: D6.1 (K), R2.1, U2.7 (HO)
unnamed: D7.2 (A), U2.3 (VCC)
unnamed: C3.1, D7.1 (K), U2.6 (VB)
unnamed: C3.2, D8.1 (K), L1.1, Q1.3 (S), U2.5 (VS)
unnamed: J2.1, R9.1, U1.16 (2IN+)
unnamed: C4.1, J2.2, L1.2, R7.2
unnamed: J3.1, R12.1
unnamed: J3.2, U1.15 (2IN-)
unnamed: J3.3, R13.2
unnamed: J4.1, R14.1
unnamed: J4.2, R16.2
unnamed: J4.3, R15.2
unnamed: C6.1, R7.1, R8.2, U1.1 (1IN+)
unnamed: R16.1, R17.2, U1.2 (1IN-)
unnamed: R4.1, U1.8 (C1), U1.11 (C2), U2.10 (HIN)
unnamed: C5.1, U1.5 (CT)
unnamed: C7.2, R10.1, R11.2, U1.4 (DTC)
unnamed: R17.1, U1.3 (FB)
unnamed: R6.2, U1.6 (RT)
unnamed: R5.2, U2.11 (SD)
VCC: C1.1, D2.1 (K), D3.1 (K), Q1.2 (D), R1.1

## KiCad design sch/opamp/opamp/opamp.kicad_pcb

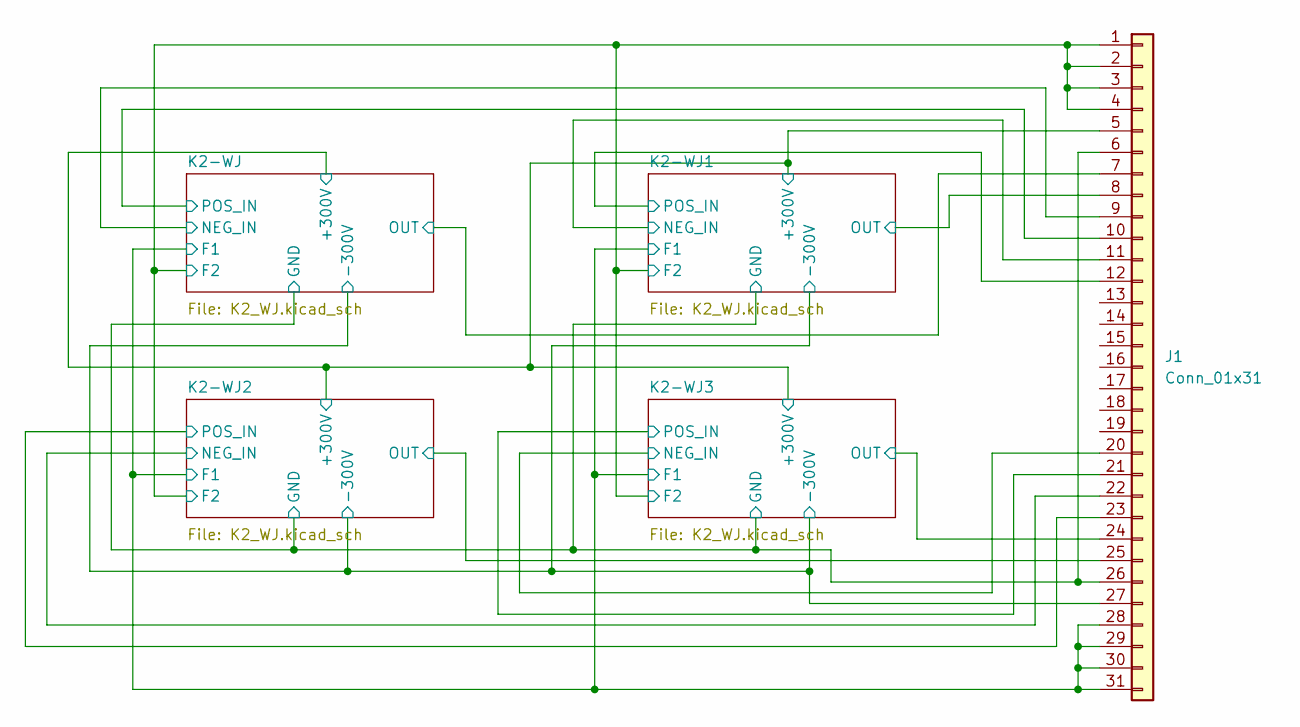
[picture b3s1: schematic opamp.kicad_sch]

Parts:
J1: Conn_01x31; ГРПМШ1-31

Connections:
/K2-WJ1/NEG_IN: J1.11; also elsewhere on the board
/K2-WJ1/OUT: J1.8; also elsewhere on the board
/K2-WJ1/POS_IN: J1.12; also elsewhere on the board
/K2-WJ2/NEG_IN: J1.22; also elsewhere on the board
/K2-WJ2/OUT: J1.25; also elsewhere on the board
/K2-WJ2/POS_IN: J1.23; also elsewhere on the board
/K2-WJ3/NEG_IN: J1.20; also elsewhere on the board
/K2-WJ3/OUT: J1.24; also elsewhere on the board
/K2-WJ3/POS_IN: J1.21; also elsewhere on the board
/K2-WJ/+300V: J1.5; also elsewhere on the board
/K2-WJ/-300V: J1.27; also elsewhere on the board
/K2-WJ/F1: J1.28, J1.29, J1.30, J1.31; also elsewhere on the board
/K2-WJ/F2: J1.1, J1.2, J1.3, J1.4; also elsewhere on the board
/K2-WJ/GND: J1.6, J1.26; also elsewhere on the board
/K2-WJ/NEG_IN: J1.9; also elsewhere on the board
/K2-WJ/OUT: J1.7; also elsewhere on the board
/K2-WJ/POS_IN: J1.10; also elsewhere on the board

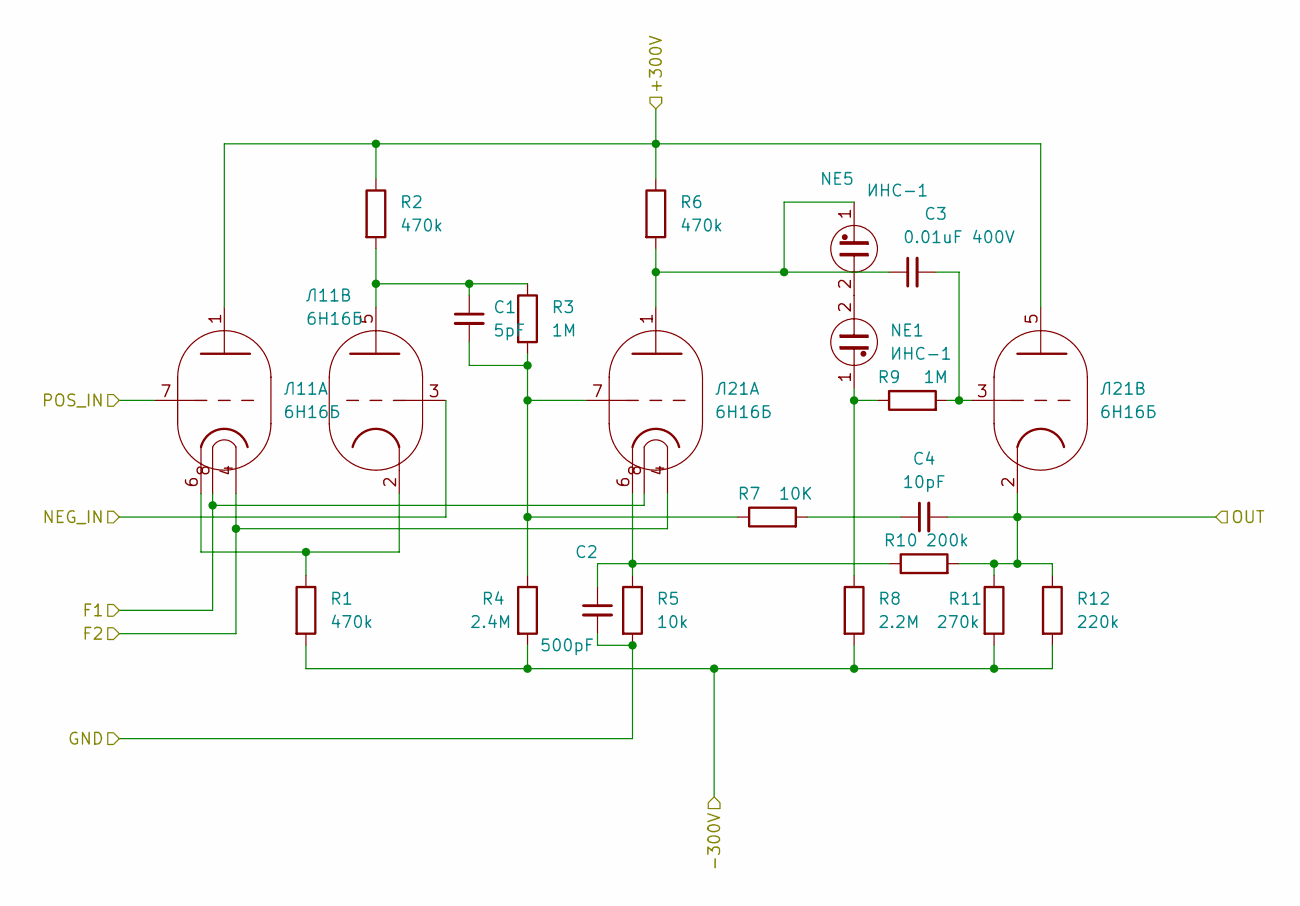
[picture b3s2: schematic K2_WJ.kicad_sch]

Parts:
C1: 5pF; C_Axial_L12.0mm_D7.5mm_P15.00mm_Horizontal
C2: 500pF; C_Axial_L22.0mm_D9.5mm_P27.50mm_Horizontal
C3: 0.01uF 400V; C_Axial_L12.0mm_D9.5mm_P15.00mm_Horizontal
C4: 10pF; C_Axial_L12.0mm_D7.5mm_P15.00mm_Horizontal
NE1, NE5: ИНС-1
R1, R2, R6: 470k; R_Axial_DIN0617_L17.0mm_D6.0mm_P20.32mm_Horizontal
R3, R9: 1M; R_Axial_DIN0617_L17.0mm_D6.0mm_P20.32mm_Horizontal
R4: 2.4M; R_Axial_DIN0617_L17.0mm_D6.0mm_P20.32mm_Horizontal
R5: 10k; R_Axial_DIN0617_L17.0mm_D6.0mm_P20.32mm_Horizontal
R7: 10K; R_Axial_DIN0617_L17.0mm_D6.0mm_P20.32mm_Horizontal
R8: 2.2M; R_Axial_DIN0617_L17.0mm_D6.0mm_P20.32mm_Horizontal
R10: 200k; R_Axial_DIN0617_L17.0mm_D6.0mm_P20.32mm_Horizontal
R11: 270k; R_Axial_DIN0617_L17.0mm_D6.0mm_P20.32mm_Horizontal
R12: 220k; R_Axial_DIN0617_L17.0mm_D6.0mm_P20.32mm_Horizontal
Л11, Л21: 6Н16Б; 6N16B

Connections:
/K2-WJ/+300V: R2.1, R6.1, Л11.1 (A), Л21.5 (A); also elsewhere on the board
/K2-WJ/-300V: R1.2, R4.2, R8.2, R11.2, R12.2; also elsewhere on the board
/K2-WJ/F1: Л11.8 (F1), Л21.8 (F1); also elsewhere on the board
/K2-WJ/F2: Л11.4 (F1), Л21.4 (F1); also elsewhere on the board
/K2-WJ/GND: C2.2, R5.2; also elsewhere on the board
/K2-WJ/NEG_IN: Л11.3 (G); also elsewhere on the board
/K2-WJ/OUT: C4.2, R10.2, R11.1, R12.1, Л21.2 (K); also elsewhere on the board
/K2-WJ/POS_IN: Л11.7 (G); also elsewhere on the board
unnamed: C4.1, R7.2
unnamed: NE1.1, R8.1, R9.1
unnamed: NE1.2, NE5.2
unnamed: R1.1, Л11.2 (K), Л11.6 (K)
unnamed: C1.1, R2.2, R3.1, Л11.5 (A)
unnamed: C3.1, NE5.1, R6.2, Л21.1 (A)
unnamed: C1.2, R3.2, R4.1, R7.1, Л21.7 (G)
unnamed: C2.1, R5.1, R10.1, Л21.6 (K)
unnamed: C3.2, R9.2, Л21.3 (G)

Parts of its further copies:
C5, C9, C13: 5pF; C_Axial_L12.0mm_D7.5mm_P15.00mm_Horizontal
C6, C10, C14: 500pF; C_Axial_L22.0mm_D9.5mm_P27.50mm_Horizontal
C7, C11, C15: 0.01uF 400V; C_Axial_L12.0mm_D9.5mm_P15.00mm_Horizontal
C8, C12, C16: 10pF; C_Axial_L12.0mm_D7.5mm_P15.00mm_Horizontal
NE2, NE3, NE4, NE6, NE7, NE8: ИНС-1
R13, R14, R18, R25, R26, R30, R37, R38, R42: 470k; R_Axial_DIN0617_L17.0mm_D6.0mm_P20.32mm_Horizontal
R15, R21, R27, R33, R39, R45: 1M; R_Axial_DIN0617_L17.0mm_D6.0mm_P20.32mm_Horizontal
R16, R28, R40: 2.4M; R_Axial_DIN0617_L17.0mm_D6.0mm_P20.32mm_Horizontal
R17, R29, R41: 10k; R_Axial_DIN0617_L17.0mm_D6.0mm_P20.32mm_Horizontal
R19, R31, R43: 10K; R_Axial_DIN0617_L17.0mm_D6.0mm_P20.32mm_Horizontal
R20, R32, R44: 2.2M; R_Axial_DIN0617_L17.0mm_D6.0mm_P20.32mm_Horizontal
R22, R34, R46: 200k; R_Axial_DIN0617_L17.0mm_D6.0mm_P20.32mm_Horizontal
R23, R35, R47: 270k; R_Axial_DIN0617_L17.0mm_D6.0mm_P20.32mm_Horizontal
R24, R36, R48: 220k; R_Axial_DIN0617_L17.0mm_D6.0mm_P20.32mm_Horizontal
Л12, Л13, Л14, Л22, Л23, Л24: 6Н16Б; 6N16B

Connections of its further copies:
/K2-WJ1/NEG_IN: Л12.3 (G); also elsewhere on the board
/K2-WJ1/OUT: C8.2, R22.2, R23.1, R24.1, Л22.2 (K); also elsewhere on the board
/K2-WJ1/POS_IN: Л12.7 (G); also elsewhere on the board
/K2-WJ2/NEG_IN: Л13.3 (G); also elsewhere on the board
/K2-WJ2/OUT: C12.2, R34.2, R35.1, R36.1, Л23.2 (K); also elsewhere on the board
/K2-WJ2/POS_IN: Л13.7 (G); also elsewhere on the board
/K2-WJ3/NEG_IN: Л14.3 (G); also elsewhere on the board
/K2-WJ3/OUT: C16.2, R46.2, R47.1, R48.1, Л24.2 (K); also elsewhere on the board
/K2-WJ3/POS_IN: Л14.7 (G); also elsewhere on the board
/K2-WJ/+300V: R14.1, R18.1, R26.1, R30.1, R38.1, R42.1, Л12.1 (A), Л13.1 (A), Л14.1 (A), Л22.5 (A), Л23.5 (A), Л24.5 (A); also elsewhere on the board
/K2-WJ/-300V: R13.2, R16.2, R20.2, R23.2, R24.2, R25.2, R28.2, R32.2, R35.2, R36.2, R37.2, R40.2, R44.2, R47.2, R48.2; also elsewhere on the board
/K2-WJ/F1: Л12.8 (F1), Л13.8 (F1), Л14.8 (F1), Л22.8 (F1), Л23.8 (F1), Л24.8 (F1); also elsewhere on the board
/K2-WJ/F2: Л12.4 (F1), Л13.4 (F1), Л14.4 (F1), Л22.4 (F1), Л23.4 (F1), Л24.4 (F1); also elsewhere on the board
/K2-WJ/GND: C6.2, C10.2, C14.2, R17.2, R29.2, R41.2; also elsewhere on the board
unnamed: C8.1, R19.2
unnamed: C12.1, R31.2
unnamed: C16.1, R43.2
unnamed: NE2.1, R20.1, R21.1
unnamed: NE2.2, NE6.2
unnamed: NE3.1, R32.1, R33.1
unnamed: NE3.2, NE7.2
unnamed: NE4.1, R44.1, R45.1
unnamed: NE4.2, NE8.2
unnamed: R13.1, Л12.2 (K), Л12.6 (K)
unnamed: C5.1, R14.2, R15.1, Л12.5 (A)
unnamed: R25.1, Л13.2 (K), Л13.6 (K)
unnamed: C9.1, R26.2, R27.1, Л13.5 (A)
unnamed: R37.1, Л14.2 (K), Л14.6 (K)
unnamed: C13.1, R38.2, R39.1, Л14.5 (A)
unnamed: C7.1, NE6.1, R18.2, Л22.1 (A)
unnamed: C5.2, R15.2, R16.1, R19.1, Л22.7 (G)
unnamed: C6.1, R17.1, R22.1, Л22.6 (K)
unnamed: C7.2, R21.2, Л22.3 (G)
unnamed: C11.1, NE7.1, R30.2, Л23.1 (A)
unnamed: C9.2, R27.2, R28.1, R31.1, Л23.7 (G)
unnamed: C10.1, R29.1, R34.1, Л23.6 (K)
unnamed: C11.2, R33.2, Л23.3 (G)
unnamed: C15.1, NE8.1, R42.2, Л24.1 (A)
unnamed: C13.2, R39.2, R40.1, R43.1, Л24.7 (G)
unnamed: C14.1, R41.1, R46.1, Л24.6 (K)
unnamed: C15.2, R45.2, Л24.3 (G)

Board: 2 copper layers, 81 parts (0 on the bottom side), 53 nets, no tracks yet.
